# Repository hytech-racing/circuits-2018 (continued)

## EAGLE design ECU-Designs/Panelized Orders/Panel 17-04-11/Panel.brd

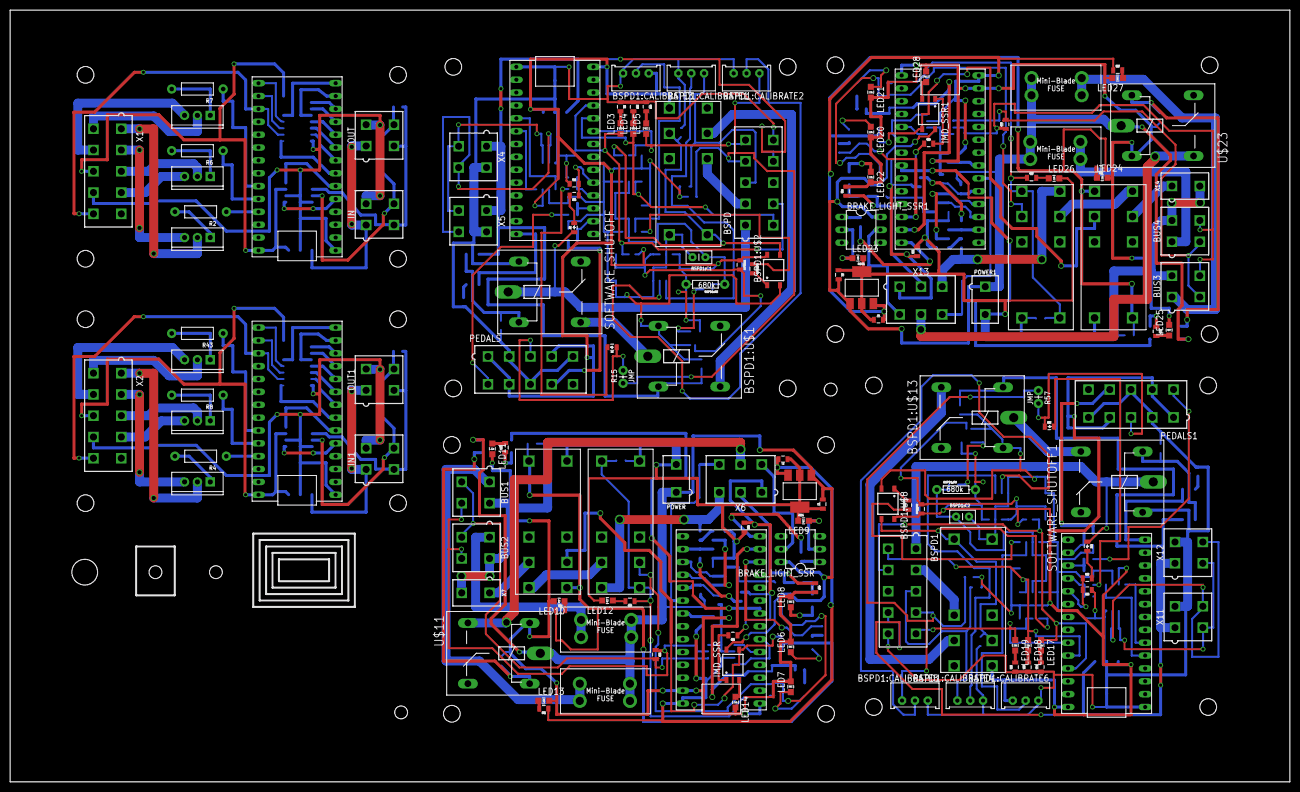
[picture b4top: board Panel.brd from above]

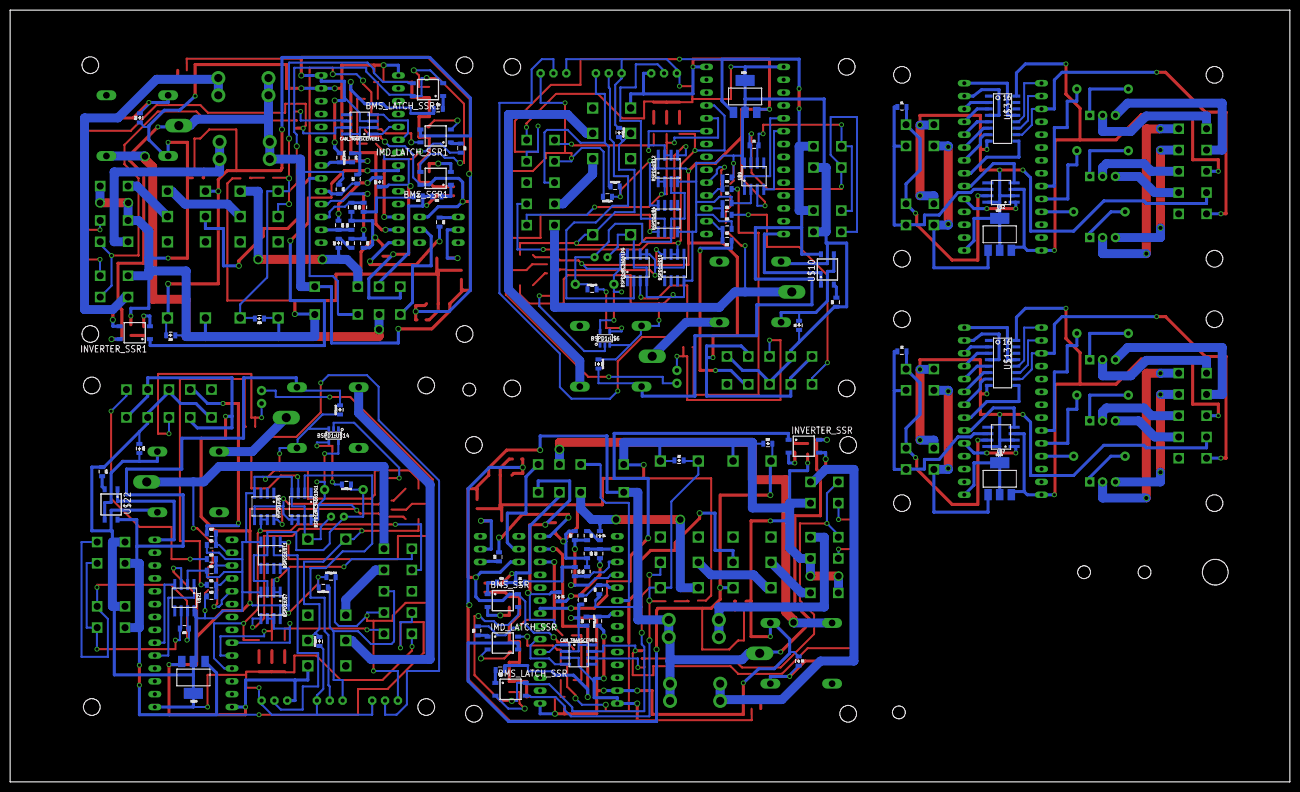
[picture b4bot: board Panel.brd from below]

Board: 2 copper layers, 252.7 x 152.4 mm, 242 parts (102 on the bottom side), 238 nets.

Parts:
BMS_LATCH_SSR, BMS_LATCH_SSR1: CPC1002N; SOP04
BMS_SSR, BMS_SSR1: CPC1002N; SOP04
BOARD_TEMP, BOARD_TEMP1: THERMISTOR_NCP21; 0805
BRAKE_LIGHT_SSR, BRAKE_LIGHT_SSR1: SOLID_STATE_RELAY_VO14642AT; DIL06
BSPD, BSPD1: MINIFIT_5566-10
BSPD1:C1, BSPD1:C2: .47u; CAP-PTH-SMALLEZ
BSPD1:CALIBRATE1, BSPD1:CALIBRATE2, BSPD1:CALIBRATE3, BSPD1:CALIBRATE4, BSPD1:CALIBRATE5, BSPD1:CALIBRATE6: TRIMPOT_3296
BSPD1:D1, BSPD1:D2, BSPD1:D3, BSPD1:D4: DIODE0805; 0805_D
BSPD1:MC34161DG, BSPD1:MC34161DG1: SOIC-08
BSPD1:R1, BSPD1:R2, BSPD1:R4, BSPD1:R7, BSPD1:R11, BSPD1:R12: 10k; 0805
BSPD1:R3, BSPD1:R8: 330; 0805
BSPD1:R5, BSPD1:R9: 680k; AXIAL-0.3EZ
BSPD1:R6, BSPD1:R10: 680; 0805
BSPD1:U$1, BSPD1:U$13: G5LE; ZF112
BSPD1:U$2, BSPD1:U$8: CPC1002N; SOP04
BSPD1:U$3, BSPD1:U$9: JW2SN-DC5V; JW2SN
BSPD1:U$4, BSPD1:U$5, BSPD1:U$7, BSPD1:U$10, BSPD1:U$11, BSPD1:U$12: MCP6002SOIC; SOIC-08
BSPD1:U$6, BSPD1:U$14: SN74LVC1G07; SOT-23-5
BUS1, BUS2, BUS3, BUS4: MINIFIT_5566-4
C1, C3: .22uF; 0805
C2, C4: .1uF; 0805
CAN_TRANSCEIVER, CAN_TRANSCEIVER1: MCP2551; SOIC-08
D2, D3, D4, D5, D6, D7, D8, D9, D10, D12, D13, D14, D15, D16, D17, D18, D19, D20: DIODE0805; 0805_D
FUSE_BUS_1, FUSE_BUS_2, FUSE_BUS_3, FUSE_BUS_4: 5A; MINI-BLADE_FUSE_HOLDER
IMD_LATCH_SSR, IMD_LATCH_SSR1: CPC1002N; SOP04
IMD_SHUTDOWN, IMD_SHUTDOWN1, IMD_SHUTDOWN2, IMD_SHUTDOWN3: G2RL-2-DC12; G2RL-2
IMD_SSR, IMD_SSR1: CPC1002N; SOP04
IN, IN1: MINIFIT_5566-4
INVERTER_SSR, INVERTER_SSR1: CPC1002N; SOP04
LED3, LED4, LED5, LED6, LED7, LED8, LED9, LED10, LED11, LED12, LED13, LED14, LED17, LED18, LED19, LED20, LED21, LED22, LED23, LED24, LED25, LED26, LED27, LED28: LED-805
OUT, OUT1: MINIFIT_5566-4
PEDALS, PEDALS1: MINIFIT_5566-10
POWER, POWER1: MINIFIT_5566-2
R1, R3, R5, R28, R50, R70: 120; 0805
R2, R4, R6, R7, R8, R43: AXIAL-0.4
R9, R13, R14, R54, R55, R56: 150; 0805
R10, R11, R12, R51, R52, R53: 15k; 0805
R15, R57: JMP; AXIAL-0.1
R16, R23, R24, R25, R26, R37, R58, R65, R66, R67, R68, R79: 100; 0805
R17, R18, R19, R36, R39, R59, R60, R61, R78, R81: 10k; 0805
R20, R22, R30, R32, R34, R62, R64, R72, R74, R76: 43k; 0805
R21, R29, R31, R33, R35, R63, R71, R73, R75, R77: 12k; 0805
R27, R38, R69, R80: 820; 0805
R40, R82: 2.2k; 0805
R41, R83: 270; 0805
R42, R84: 680; 0805
REG, REG1: 5V; SOT223
SOFTWARE_SHUTOFF, SOFTWARE_SHUTOFF1: G5LE; ZF112
T1, T2, T3, T4, T5, T6: N-CHANNEL_MOSFETGENERIC; TO-220-SINK
U$1, U$4, U$6, U$12, U$19, U$24: TEENSY_3.2_SIMPLE
U$2, U$7, U$9, U$21: MCP2551; SOIC-08
U$3, U$13: CD4040BSOIC; SOIC-16
U$5, U$8, U$14, U$20: SOT223
U$10, U$22: CPC1002N; SOP04
U$11, U$23: G5LE; ZF112
X1, X2: CONNECTOR-10; MINIFIT_5566-10
X4, X5, X11, X12: MINIFIT_5566-4
X6, X13: MINIFIT_5566-6
X7, X14: MINIFIT_5566-2

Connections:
12VSUPPLY_READ: R34.2, R35.1, U$12.A3
12VSUPPLY_READ1: R76.2, R77.1, U$24.A3
12V_F1: BUS1.1, FUSE_BUS_1.L1, FUSE_BUS_1.L2
12V_F2: BUS2.1, FUSE_BUS_2.R1, FUSE_BUS_2.R2
12V_F3: BUS3.1, FUSE_BUS_3.L1, FUSE_BUS_3.L2
12V_F4: BUS4.1, FUSE_BUS_4.R1, FUSE_BUS_4.R2
+5V: BSPD1:CALIBRATE3.1, BSPD1:MC34161DG.8, BSPD1:R1.1, BSPD1:R4.1, BSPD1:R5.P$2, BSPD1:R7.2, BSPD1:U$2.4, BSPD1:U$3.4, BSPD1:U$4.8, BSPD1:U$6.5, BSPD1:U$10.8, BSPD1:U$12.8, PEDALS.1, PEDALS.4, PEDALS.7, U$4.VIN, U$8.3, U$9.3
+5V1: BOARD_TEMP.1, C2.2, CAN_TRANSCEIVER.3, R41.1, REG.3, U$12.VIN
+5V2: BSPD1:CALIBRATE6.1, BSPD1:MC34161DG1.8, BSPD1:R2.1, BSPD1:R9.P$2, BSPD1:R11.1, BSPD1:R12.2, BSPD1:U$5.8, BSPD1:U$7.8, BSPD1:U$8.4, BSPD1:U$9.4, BSPD1:U$11.8, BSPD1:U$14.5, PEDALS1.1, PEDALS1.4, PEDALS1.7, U$19.VIN, U$20.3, U$21.3
+5V3: BOARD_TEMP1.1, C4.2, CAN_TRANSCEIVER1.3, R83.1, REG1.3, U$24.VIN
+5V4: U$1.VIN, U$2.3, U$3.16, U$5.3, X1.8
+5V5: U$6.VIN, U$7.3, U$13.16, U$14.3, X2.8
+12V: IN.1, OUT.1, U$5.1
+12V1: BSPD.9, BSPD1:D2.C, BSPD1:U$1.2, U$8.1, U$10.4, X4.1, X5.1
+12V2: BMS_SSR.4, BRAKE_LIGHT_SSR.6, C1.2, FUSE_BUS_1.R1, FUSE_BUS_1.R2, FUSE_BUS_2.L1, FUSE_BUS_2.L2, IMD_SSR.4, INVERTER_SSR.4, POWER.1, R34.1, REG.1, U$11.P
+12V3: IN1.1, OUT1.1, U$14.1
+12V4: BSPD1.9, BSPD1:D4.C, BSPD1:U$13.2, U$20.1, U$22.4, X11.1, X12.1
+12V5: BMS_SSR1.4, BRAKE_LIGHT_SSR1.6, C3.2, FUSE_BUS_3.R1, FUSE_BUS_3.R2, FUSE_BUS_4.L1, FUSE_BUS_4.L2, IMD_SSR1.4, INVERTER_SSR1.4, POWER1.1, R76.1, REG1.1, U$23.P
BMS_COIL_PWR: BMS_LATCH_SSR.3, D9.C, IMD_SHUTDOWN1.4, IMD_SHUTDOWN1.COIL-, R38.1
BMS_COIL_PWR1: BMS_LATCH_SSR1.3, D19.C, IMD_SHUTDOWN3.4, IMD_SHUTDOWN3.COIL-, R80.1
BMS_OK: D6.A, R24.2, R39.1, X6.2
BMS_OK1: D16.A, R66.2, R81.1, X13.2
BMS_OK_READ: R30.2, R31.1, U$12.A1
BMS_OK_READ1: R72.2, R73.1, U$24.A1
BMS_PWR_STEP: BMS_LATCH_SSR.4, BMS_SSR.3, IMD_SHUTDOWN1.3
BMS_PWR_STEP1: BMS_LATCH_SSR1.4, BMS_SSR1.3, IMD_SHUTDOWN3.3
BSPD1:N$1: BSPD1:D1.C, BSPD1:U$2.3, BSPD1:U$3.3, BSPD1:U$3.COIL-, BSPD1:U$12.5
BSPD1:N$2: BSPD1:R3.2, BSPD1:U$6.4
BSPD1:N$3: BSPD1:R6.2, BSPD1:U$2.1
BSPD1:N$4: BSPD1:CALIBRATE5.2, BSPD1:MC34161DG1.3
BSPD1:N$5: BSPD1:CALIBRATE2.2, BSPD1:MC34161DG.3
BSPD1:N$6: BSPD1:CALIBRATE1.2, BSPD1:MC34161DG.2
BSPD1:N$7: BSPD1:CALIBRATE3.2, BSPD1:U$4.2
BSPD1:N$8: BSPD1:CALIBRATE4.2, BSPD1:MC34161DG1.2
BSPD1:N$9: BSPD1:R6.1, BSPD1:U$4.1
BSPD1:N$10: BSPD1:MC34161DG.5, BSPD1:MC34161DG.6, BSPD1:R1.2, BSPD1:U$6.2, BSPD1:U$10.5
BSPD1:N$11: BSPD1:R10.1, BSPD1:U$11.1
BSPD1:N$12: BSPD1:C2.1, BSPD1:R8.1, BSPD1:R9.P$1, BSPD1:U$7.3, BSPD1:U$11.3
BSPD1:N$13: BSPD1:C1.1, BSPD1:R3.1, BSPD1:R5.P$1, BSPD1:U$4.3, BSPD1:U$12.3
BSPD1:N$14: BSPD1:CALIBRATE6.2, BSPD1:U$11.2
BSPD1:N$15: BSPD1:D3.C, BSPD1:U$7.5, BSPD1:U$8.3, BSPD1:U$9.3, BSPD1:U$9.COIL-
BSPD1:N$16: BSPD1:MC34161DG1.5, BSPD1:MC34161DG1.6, BSPD1:R2.2, BSPD1:U$5.5, BSPD1:U$14.2
BSPD1:N$17: BSPD1:R8.2, BSPD1:U$14.4
BSPD1:N$18: BSPD1:R10.2, BSPD1:U$8.1
BSPD1:SHUTDOWN_C: BSPD1:U$1.S, BSPD1:U$3.6
BSPD1:SHUTDOWN_C1: BSPD1:U$9.6, BSPD1:U$13.S
CANH: BUS1.4, BUS2.4, CAN_TRANSCEIVER.7, R28.1
CANH1: BUS3.4, BUS4.4, CAN_TRANSCEIVER1.7, R70.1
CANH2: IN.4, OUT.4, R1.2, U$2.7
CANH3: IN1.4, OUT1.4, R3.2, U$7.7
CANL: BUS1.3, BUS2.3, CAN_TRANSCEIVER.6, R28.2
CANL1: BUS3.3, BUS4.3, CAN_TRANSCEIVER1.6, R70.2
CANL2: IN.3, OUT.3, R1.1, U$2.6
CANL3: IN1.3, OUT1.3, R3.1, U$7.6
FAN1-: T1.2, X1.1
FAN1-1: T4.2, X2.1
FAN2-: T2.2, X1.3
FAN2-1: T5.2, X2.3
FAN3-: T3.2, X1.6
FAN3-1: T6.2, X2.6
GND: IN.2, OUT.2, U$1.GND, U$2.2, U$2.8, U$3.8, U$5.2, U$5.4, X1.9
GND1: BSPD.10, BSPD1:C1.2, BSPD1:CALIBRATE1.3, BSPD1:CALIBRATE2.3, BSPD1:CALIBRATE3.3, BSPD1:D1.A, BSPD1:D2.A, BSPD1:MC34161DG.4, BSPD1:MC34161DG.7, BSPD1:U$1.1, BSPD1:U$2.2, BSPD1:U$3.COIL+, BSPD1:U$4.4, BSPD1:U$6.3, BSPD1:U$10.4, BSPD1:U$12.4, D4.A, PEDALS.2, PEDALS.5, PEDALS.8, R9.1, R10.1, R11.1, R12.1, R13.1, R14.1, R16.1, R21.1, SOFTWARE_SHUTOFF.1, U$4.GND, U$8.2, U$8.4, U$9.2, U$9.8, X4.2, X5.2
GND2: BUS1.2, BUS2.2, C1.1, C2.1, CAN_TRANSCEIVER.2, CAN_TRANSCEIVER.8, D8.A, D9.A, D10.A, IMD_SHUTDOWN.COIL+, IMD_SHUTDOWN1.COIL+, LED6.C, LED7.C, LED8.C, LED9.C, LED10.C, LED11.C, LED12.C, LED13.C, LED14.C, POWER.2, R29.2, R31.2, R33.2, R35.2, R36.1, R39.2, R40.2, REG.2, REG.4, U$11.2, U$12.AGND, U$12.GND, X7.2
GND3: T1.3, X1.2
GND4: BSPD1.10, BSPD1:C2.2, BSPD1:CALIBRATE4.3, BSPD1:CALIBRATE5.3, BSPD1:CALIBRATE6.3, BSPD1:D3.A, BSPD1:D4.A, BSPD1:MC34161DG1.4, BSPD1:MC34161DG1.7, BSPD1:U$5.4, BSPD1:U$7.4, BSPD1:U$8.2, BSPD1:U$9.COIL+, BSPD1:U$11.4, BSPD1:U$13.1, BSPD1:U$14.3, D14.A, PEDALS1.2, PEDALS1.5, PEDALS1.8, R51.1, R52.1, R53.1, R54.1, R55.1, R56.1, R58.1, R63.1, SOFTWARE_SHUTOFF1.1, U$19.GND, U$20.2, U$20.4, U$21.2, U$21.8, X11.2, X12.2
GND5: BUS3.2, BUS4.2, C3.1, C4.1, CAN_TRANSCEIVER1.2, CAN_TRANSCEIVER1.8, D18.A, D19.A, D20.A, IMD_SHUTDOWN2.COIL+, IMD_SHUTDOWN3.COIL+, LED20.C, LED21.C, LED22.C, LED23.C, LED24.C, LED25.C, LED26.C, LED27.C, LED28.C, POWER1.2, R71.2, R73.2, R75.2, R77.2, R78.1, R81.2, R82.2, REG1.2, REG1.4, U$23.2, U$24.AGND, U$24.GND, X14.2
GND6: T2.3, X1.4
GND7: T3.3, X1.7
GND8: IN1.2, OUT1.2, U$6.GND, U$7.2, U$7.8, U$13.8, U$14.2, U$14.4, X2.9
GND9: T4.3, X2.2
GND10: T5.3, X2.4
GND11: T6.3, X2.7
INVERTER_SUPPLY: U$11.S, X6.5
INVERTER_SUPPLY1: U$23.S, X13.5
unnamed: R2.P$2, T1.1
unnamed: U$1.D3(CANTX), U$2.1
unnamed: U$1.D4(CANRX), U$2.4
unnamed: R6.P$2, T2.1
unnamed: R7.P$1, U$1.A7
unnamed: R7.P$2, T3.1
unnamed: U$1.D7(RX3), U$3.6
unnamed: U$6.D3(CANTX), U$7.1
unnamed: U$6.D4(CANRX), U$7.4
unnamed: R4.P$2, T4.1
unnamed: R8.P$2, T5.1
unnamed: U$1.D5, U$3.9
unnamed: U$1.D6, U$3.7
unnamed: R5.2, U$9.6, X4.3, X5.3
unnamed: U$1.D8(TX3), U$3.5
unnamed: U$1.D9(RX2), U$3.3
unnamed: U$1.D10(TX2), U$3.2
unnamed: R2.P$1, U$1.A9
unnamed: R6.P$1, U$1.A8
unnamed: R5.1, U$9.7, X4.4, X5.4
unnamed: U$1.D11, U$3.4
unnamed: U$1.D12, U$3.13
unnamed: U$1.A0, U$3.11
unnamed: U$1.D13, U$3.12
unnamed: R43.P$2, T6.1
unnamed: U$4.D4(CANRX), U$9.4
unnamed: U$4.D3(CANTX), U$9.1
unnamed: PEDALS.6, R18.1
unnamed: R10.2, R17.2, U$4.A0
unnamed: LED3.C, R9.2
unnamed: LED4.C, R13.2
unnamed: LED5.C, R14.2
unnamed: R16.2, U$10.2
unnamed: R11.2, R18.2, U$4.A1
unnamed: PEDALS.9, R17.1
unnamed: R12.2, R19.2, U$4.A2
unnamed: D2.A, PEDALS.3, R15.P$2
unnamed: D2.C, R19.1
unnamed: D4.C, SOFTWARE_SHUTOFF.2, U$10.3
unnamed: D3.C, R20.2
unnamed: CAN_TRANSCEIVER.4, U$12.D4(CANRX)
unnamed: CAN_TRANSCEIVER.1, U$12.D3(CANTX)
unnamed: D10.C, IMD_LATCH_SSR.3, IMD_SHUTDOWN.4, IMD_SHUTDOWN.COIL-, R27.1
unnamed: R23.2, U$12.D12
unnamed: BRAKE_LIGHT_SSR.5, X6.4
unnamed: BOARD_TEMP.2, R36.2, U$12.A5
unnamed: R26.1, U$12.D11
unnamed: IMD_LATCH_SSR.2, LED6.A
unnamed: BMS_SSR.2, LED8.A
unnamed: BMS_SSR.1, R24.1
unnamed: BRAKE_LIGHT_SSR.2, LED9.A
unnamed: BRAKE_LIGHT_SSR.1, R23.1
unnamed: LED10.A, R27.2
unnamed: INVERTER_SSR.1, U$12.D6
unnamed: U$12.A4, X6.6
unnamed: D5.C, R22.1
unnamed: D6.C, R30.1
unnamed: D7.C, R32.1
unnamed: D8.C, INVERTER_SSR.3, U$11.1
unnamed: INVERTER_SSR.2, R37.1
unnamed: LED11.A, R37.2
unnamed: IMD_LATCH_SSR.1, R25.1
unnamed: R25.2, U$12.D10(TX2)
unnamed: BMS_LATCH_SSR.2, LED7.A
unnamed: BMS_LATCH_SSR.1, R26.2
unnamed: LED12.A, R38.2
unnamed: LED13.A, R41.2
unnamed: IMD_LATCH_SSR.4, IMD_SHUTDOWN.3, IMD_SSR.3
unnamed: IMD_SSR.2, LED14.A
unnamed: IMD_SSR.1, R42.2
unnamed: R4.P$1, U$6.A9
unnamed: R8.P$1, U$6.A8
unnamed: R43.P$1, U$6.A7
unnamed: U$6.D5, U$13.9
unnamed: U$6.D6, U$13.7
unnamed: U$6.D7(RX3), U$13.6
unnamed: U$6.D8(TX3), U$13.5
unnamed: U$6.D9(RX2), U$13.3
unnamed: U$6.D10(TX2), U$13.2
unnamed: U$6.D11, U$13.4
unnamed: U$6.D12, U$13.13
unnamed: U$6.A0, U$13.11
unnamed: U$6.D13, U$13.12
unnamed: R50.2, U$21.6, X11.3, X12.3
unnamed: R50.1, U$21.7, X11.4, X12.4
unnamed: U$19.D4(CANRX), U$21.4
unnamed: U$19.D3(CANTX), U$21.1
unnamed: PEDALS1.6, R60.1
unnamed: R51.2, R59.2, U$19.A0
unnamed: LED17.C, R54.2
unnamed: LED18.C, R55.2
unnamed: LED19.C, R56.2
unnamed: R58.2, U$22.2
unnamed: R52.2, R60.2, U$19.A1
unnamed: PEDALS1.9, R59.1
unnamed: R53.2, R61.2, U$19.A2
unnamed: D12.A, PEDALS1.3, R57.P$2
unnamed: D12.C, R61.1
unnamed: D14.C, SOFTWARE_SHUTOFF1.2, U$22.3
unnamed: D13.C, R62.2
unnamed: CAN_TRANSCEIVER1.4, U$24.D4(CANRX)
unnamed: CAN_TRANSCEIVER1.1, U$24.D3(CANTX)
unnamed: D20.C, IMD_LATCH_SSR1.3, IMD_SHUTDOWN2.4, IMD_SHUTDOWN2.COIL-, R69.1
unnamed: R65.2, U$24.D12
unnamed: BRAKE_LIGHT_SSR1.5, X13.4
unnamed: BOARD_TEMP1.2, R78.2, U$24.A5
unnamed: R68.1, U$24.D11
unnamed: IMD_LATCH_SSR1.2, LED20.A
unnamed: BMS_SSR1.2, LED22.A
unnamed: BMS_SSR1.1, R66.1
unnamed: BRAKE_LIGHT_SSR1.2, LED23.A
unnamed: BRAKE_LIGHT_SSR1.1, R65.1
unnamed: LED24.A, R69.2
unnamed: INVERTER_SSR1.1, U$24.D6
unnamed: U$24.A4, X13.6
unnamed: D15.C, R64.1
unnamed: D16.C, R72.1
unnamed: D17.C, R74.1
unnamed: D18.C, INVERTER_SSR1.3, U$23.1
unnamed: INVERTER_SSR1.2, R79.1
unnamed: LED25.A, R79.2
unnamed: IMD_LATCH_SSR1.1, R67.1
unnamed: R67.2, U$24.D10(TX2)
unnamed: BMS_LATCH_SSR1.2, LED21.A
unnamed: BMS_LATCH_SSR1.1, R68.2
unnamed: LED26.A, R80.2
unnamed: LED27.A, R83.2
unnamed: IMD_LATCH_SSR1.4, IMD_SHUTDOWN2.3, IMD_SSR1.3
unnamed: IMD_SSR1.2, LED28.A
unnamed: IMD_SSR1.1, R84.2
OKHS: D5.A, R40.1, R42.1, X6.1
OKHS1: D15.A, R82.1, R84.1, X13.1
OKHS_READ: R22.2, R29.1, U$12.A0
OKHS_READ1: R64.2, R71.1, U$24.A0
PULSE: U$1.A1, U$3.10, X1.10
PULSE1: U$6.A1, U$13.10, X2.10
READ_CHARGE: BSPD.6, BSPD1:U$12.1, BSPD1:U$12.2, LED4.A, U$4.A8
READ_CHARGE1: BSPD1.6, BSPD1:U$7.1, BSPD1:U$7.2, LED18.A, U$19.A8
READ_FAULT: BSPD.5, BSPD1:U$12.6, BSPD1:U$12.7, LED5.A, U$4.A7
READ_FAULT1: BSPD1.5, BSPD1:U$7.6, BSPD1:U$7.7, LED19.A, U$19.A7
READ_SWITCH: BSPD.7, BSPD1:U$10.6, BSPD1:U$10.7, LED3.A, U$4.A9
READ_SWITCH1: BSPD1.7, BSPD1:U$5.6, BSPD1:U$5.7, LED17.A, U$19.A9
READ_UPSTREAM_SHUTDOWN: R20.1, R21.2, U$4.A3
READ_UPSTREAM_SHUTDOWN1: R62.1, R63.2, U$19.A3
SHUTDOWN_A: BSPD.1, D3.A, SOFTWARE_SHUTOFF.P
SHUTDOWN_A1: IMD_SHUTDOWN.5, IMD_SHUTDOWN1.6
SHUTDOWN_A2: BSPD1.1, D13.A, SOFTWARE_SHUTOFF1.P
SHUTDOWN_A3: IMD_SHUTDOWN2.5, IMD_SHUTDOWN3.6
SHUTDOWN_B: BSPD1:U$1.P, SOFTWARE_SHUTOFF.S
SHUTDOWN_B1: D7.A, IMD_SHUTDOWN1.5, X6.3
SHUTDOWN_B2: BSPD1:U$13.P, SOFTWARE_SHUTOFF1.S
SHUTDOWN_B3: D17.A, IMD_SHUTDOWN3.5, X13.3
SHUTDOWN_D: BSPD.2, BSPD1:U$3.7
SHUTDOWN_D1: BSPD1.2, BSPD1:U$9.7
SHUTDOWN_OUT_READ: R32.2, R33.1, U$12.A2
SHUTDOWN_OUT_READ1: R74.2, R75.1, U$24.A2
SHUTDOWN_POWER: IMD_SHUTDOWN.6, X7.1
SHUTDOWN_POWER1: IMD_SHUTDOWN2.6, X14.1
SHUTDOWN_RELAY_CTRL: U$4.D12, U$10.1
SHUTDOWN_RELAY_CTRL1: U$19.D12, U$22.1
SIGNAL_BRAKE: BSPD.4, BSPD1:CALIBRATE2.1, BSPD1:R4.2, R15.P$1
SIGNAL_BRAKE1: BSPD1.4, BSPD1:CALIBRATE5.1, BSPD1:R11.2, R57.P$1
SIGNAL_CURRENT: BSPD.3, BSPD1:CALIBRATE1.1, BSPD1:R7.1
SIGNAL_CURRENT1: BSPD1.3, BSPD1:CALIBRATE4.1, BSPD1:R12.1

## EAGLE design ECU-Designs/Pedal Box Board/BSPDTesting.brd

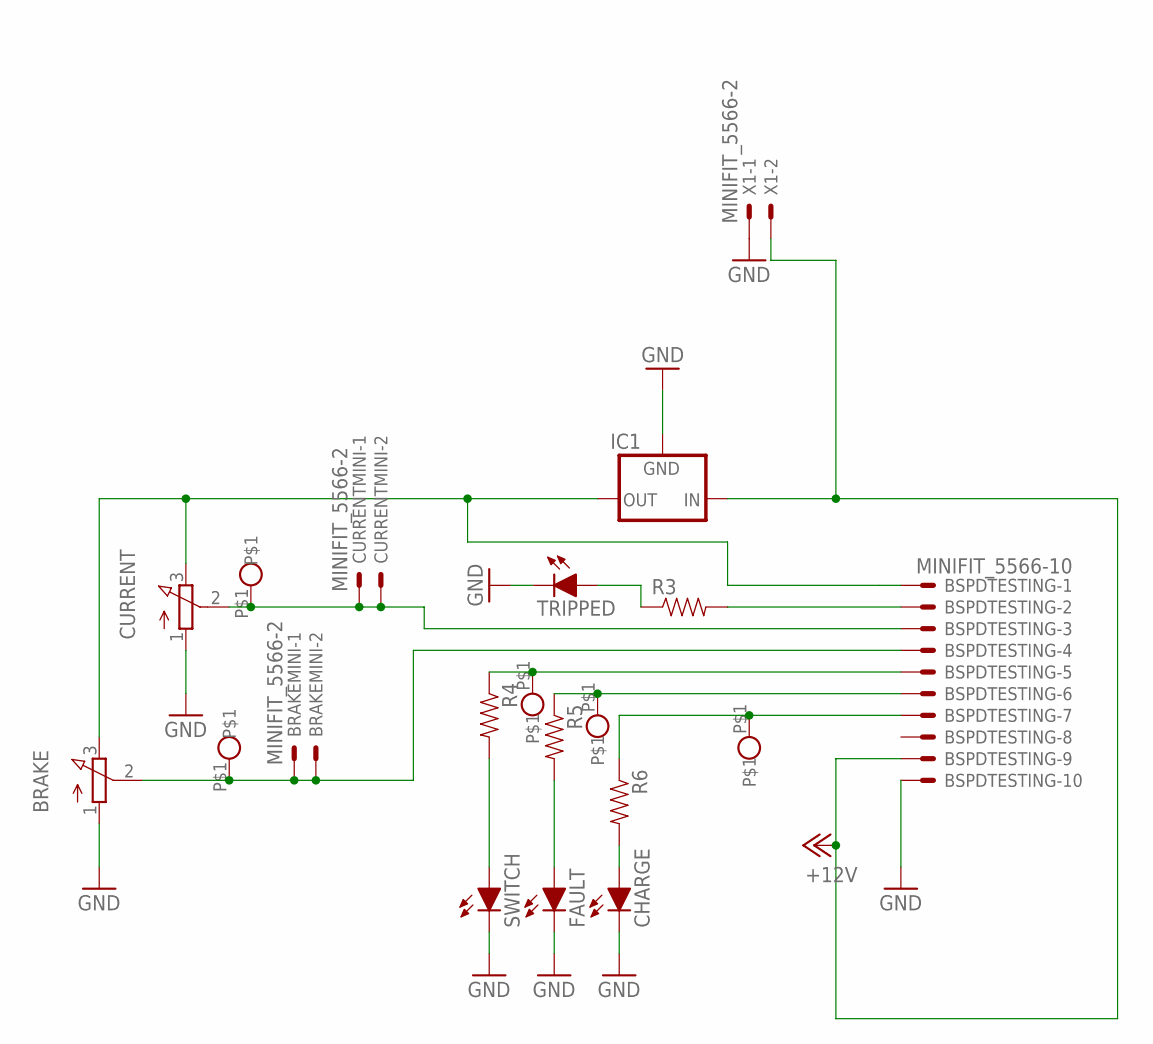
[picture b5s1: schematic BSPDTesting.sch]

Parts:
BRAKE: 3RP/1610N
BRAKEMINI: MINIFIT_5566-2
BSPDTESTING: MINIFIT_5566-10
CHARGE: LED-3MM
CURRENT: 3RP/1610N
CURRENTMINI: MINIFIT_5566-2
FAULT: LED-3MM
IC1: 5VREG_L7805_HOR; TO-220-H
R3, R4, R5, R6: RESISTORAXIAL-0.3; AXIAL-0.3
SWITCH: LED-3MM
TRIPPED: LED-3MM
U$1, U$2, U$3, U$4, U$5: TEST_POINT_COMPACT_THM
X1: MINIFIT_5566-2

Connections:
+12V: BSPDTESTING.9, IC1.1 (IN), X1.2
GND: BRAKE.1 (A), BSPDTESTING.10, CHARGE.K (C), CURRENT.1 (A), FAULT.K (C), IC1.2 (GND), SWITCH.K (C), TRIPPED.K (C), X1.1
unnamed: BSPDTESTING.5, R4.P$1 (1), U$3.P$1
unnamed: R4.P$2 (2), SWITCH.A
unnamed: BSPDTESTING.6, R5.P$1 (1), U$4.P$1
unnamed: FAULT.A, R5.P$2 (2)
unnamed: BSPDTESTING.7, R6.P$1 (1), U$5.P$1
unnamed: CHARGE.A, R6.P$2 (2)
unnamed: BSPDTESTING.2, R3.P$2 (2)
unnamed: R3.P$1 (1), TRIPPED.A
unnamed: BRAKE.2 (S), BRAKEMINI.1, BRAKEMINI.2, BSPDTESTING.4, U$1.P$1
unnamed: BSPDTESTING.3, CURRENT.2 (S), CURRENTMINI.1, CURRENTMINI.2, U$2.P$1
unnamed: BRAKE.3 (E), CURRENT.3 (E), IC1.3 (OUT)

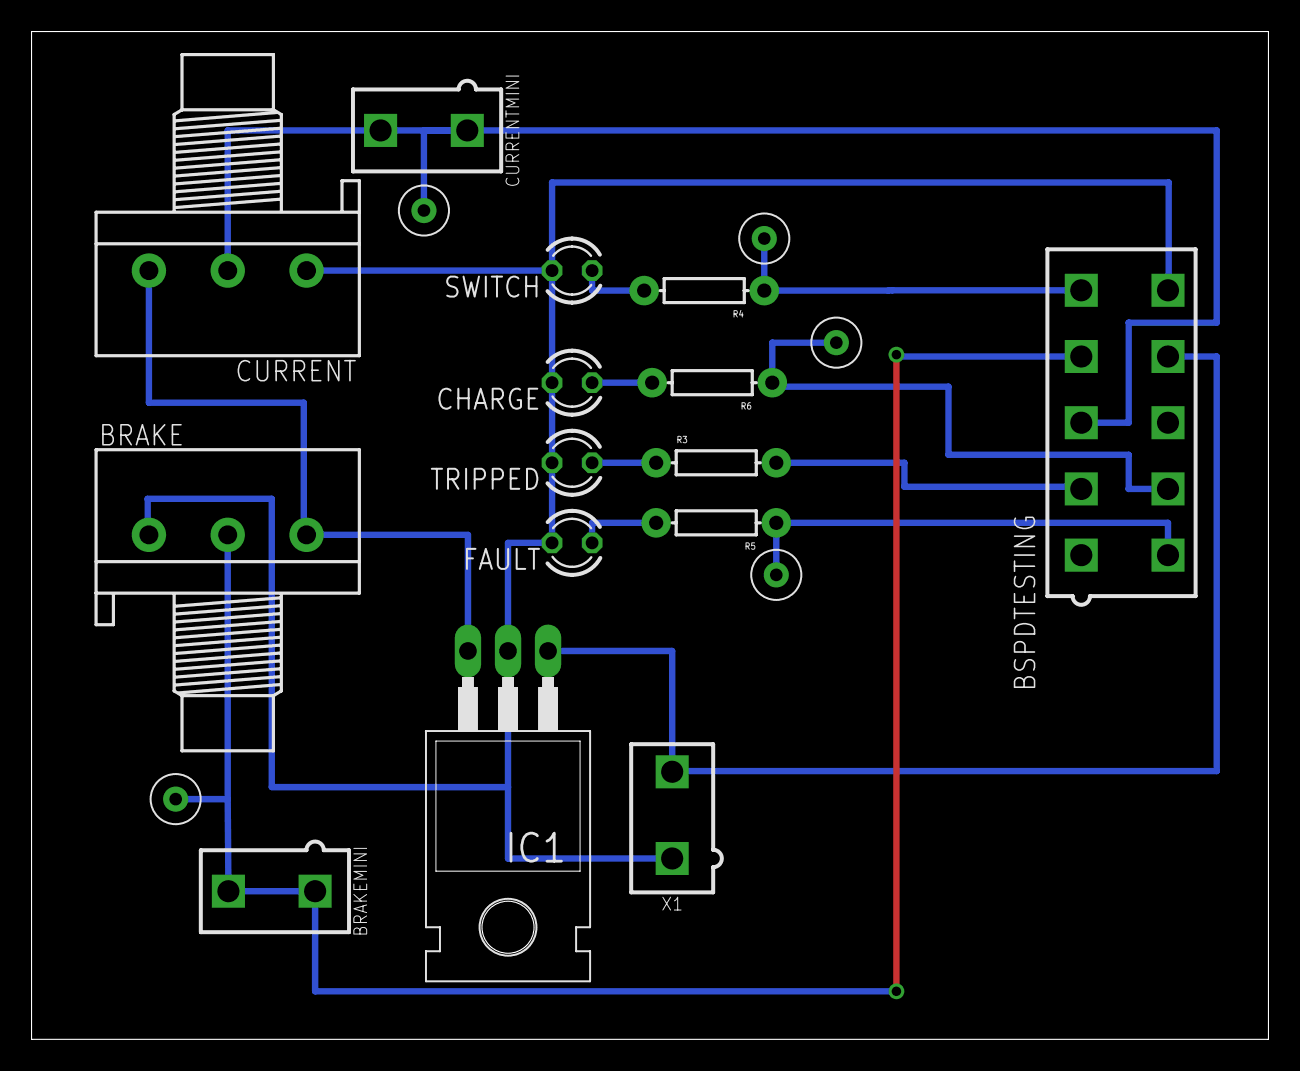
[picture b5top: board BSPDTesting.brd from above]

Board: 2 copper layers, 78.5 x 63.9 mm, 20 parts (0 on the bottom side), 13 nets.

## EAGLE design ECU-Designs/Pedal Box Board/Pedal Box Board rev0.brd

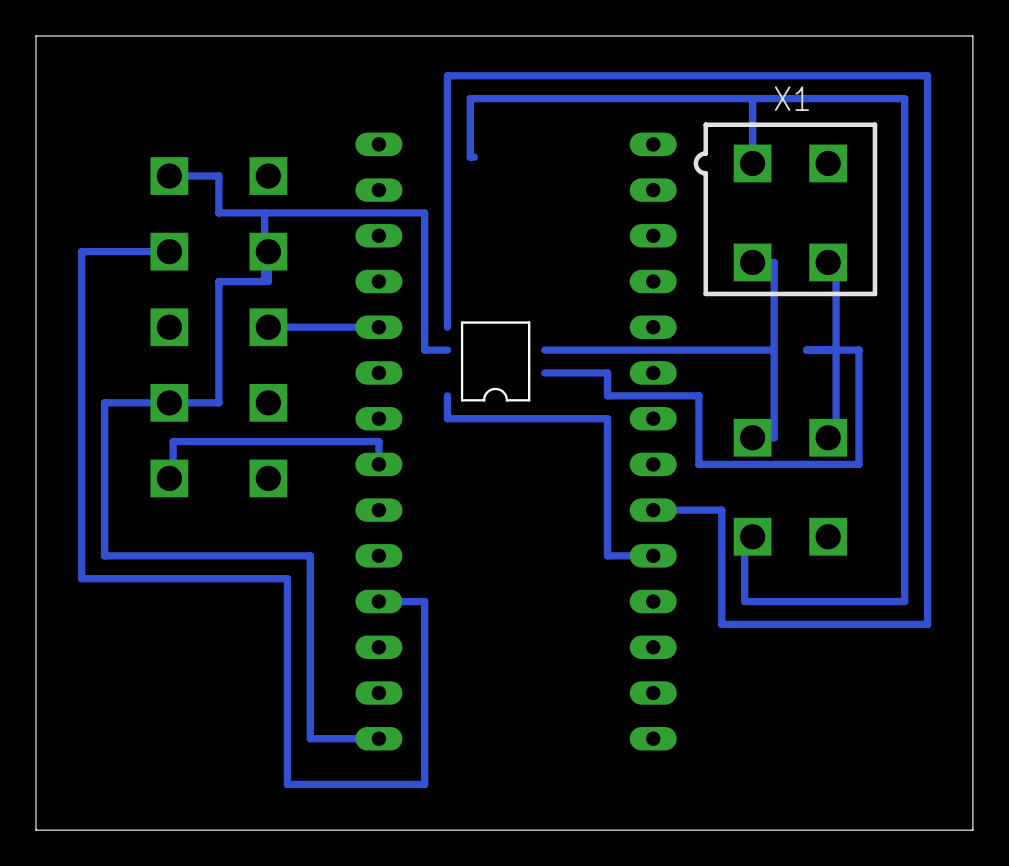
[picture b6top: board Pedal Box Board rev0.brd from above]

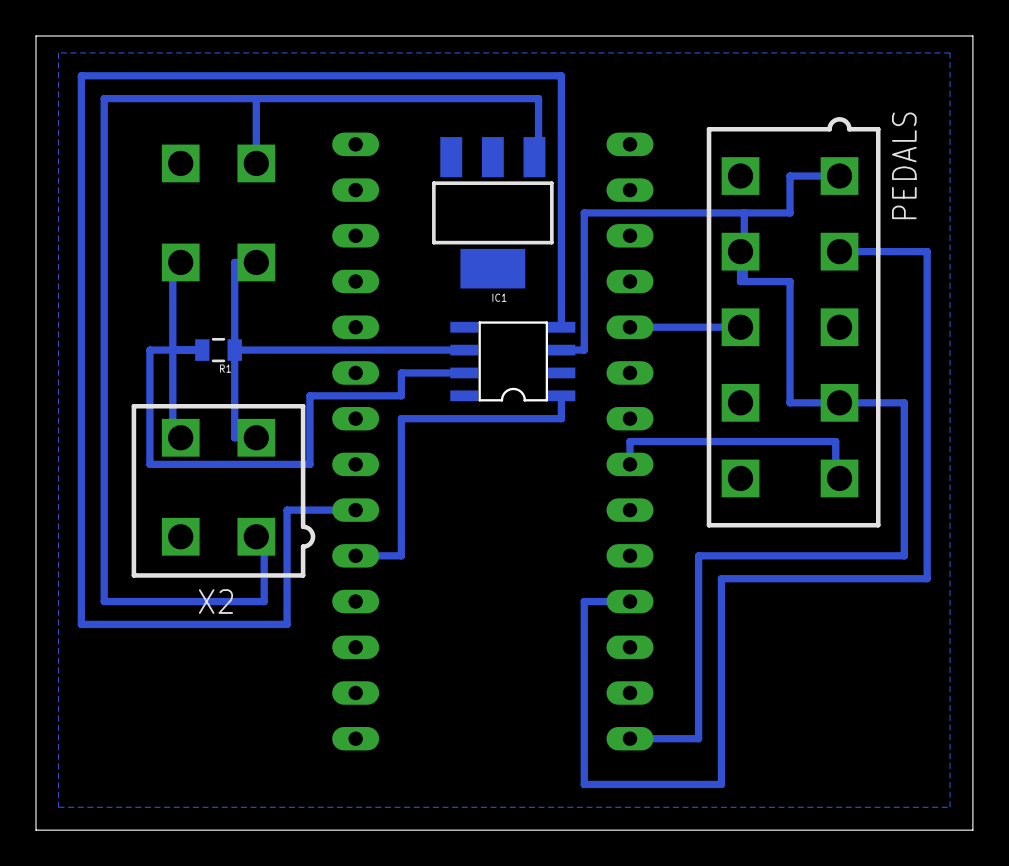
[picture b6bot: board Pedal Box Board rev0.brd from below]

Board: 2 copper layers, 52.0 x 44.1 mm, 7 parts (5 on the bottom side), 10 nets.

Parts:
IC1: SOT223
PEDALS: MINIFIT_5566-10
R1: 120; 0805
U$1: TEENSY_3.2_SIMPLE
U$2: MCP2551SOIC; SOIC08
X1, X2: MINIFIT_5566-4

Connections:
GND: IC1.2, IC1.4, PEDALS.3, PEDALS.6, PEDALS.9, U$1.GND, U$2.2, X2.2
unnamed: R1.2, U$2.7, X1.4, X2.4
unnamed: R1.1, U$2.6, X1.3, X2.3
unnamed: PEDALS.2, U$1.A9
unnamed: IC1.1, X1.1, X2.1
unnamed: PEDALS.5, U$1.A6
unnamed: PEDALS.8, U$1.A3
unnamed: PEDALS.1, PEDALS.4, PEDALS.7, U$1.VIN, U$2.3
unnamed: U$1.D4(CANRX), U$2.4
unnamed: U$1.D3(CANTX), U$2.1

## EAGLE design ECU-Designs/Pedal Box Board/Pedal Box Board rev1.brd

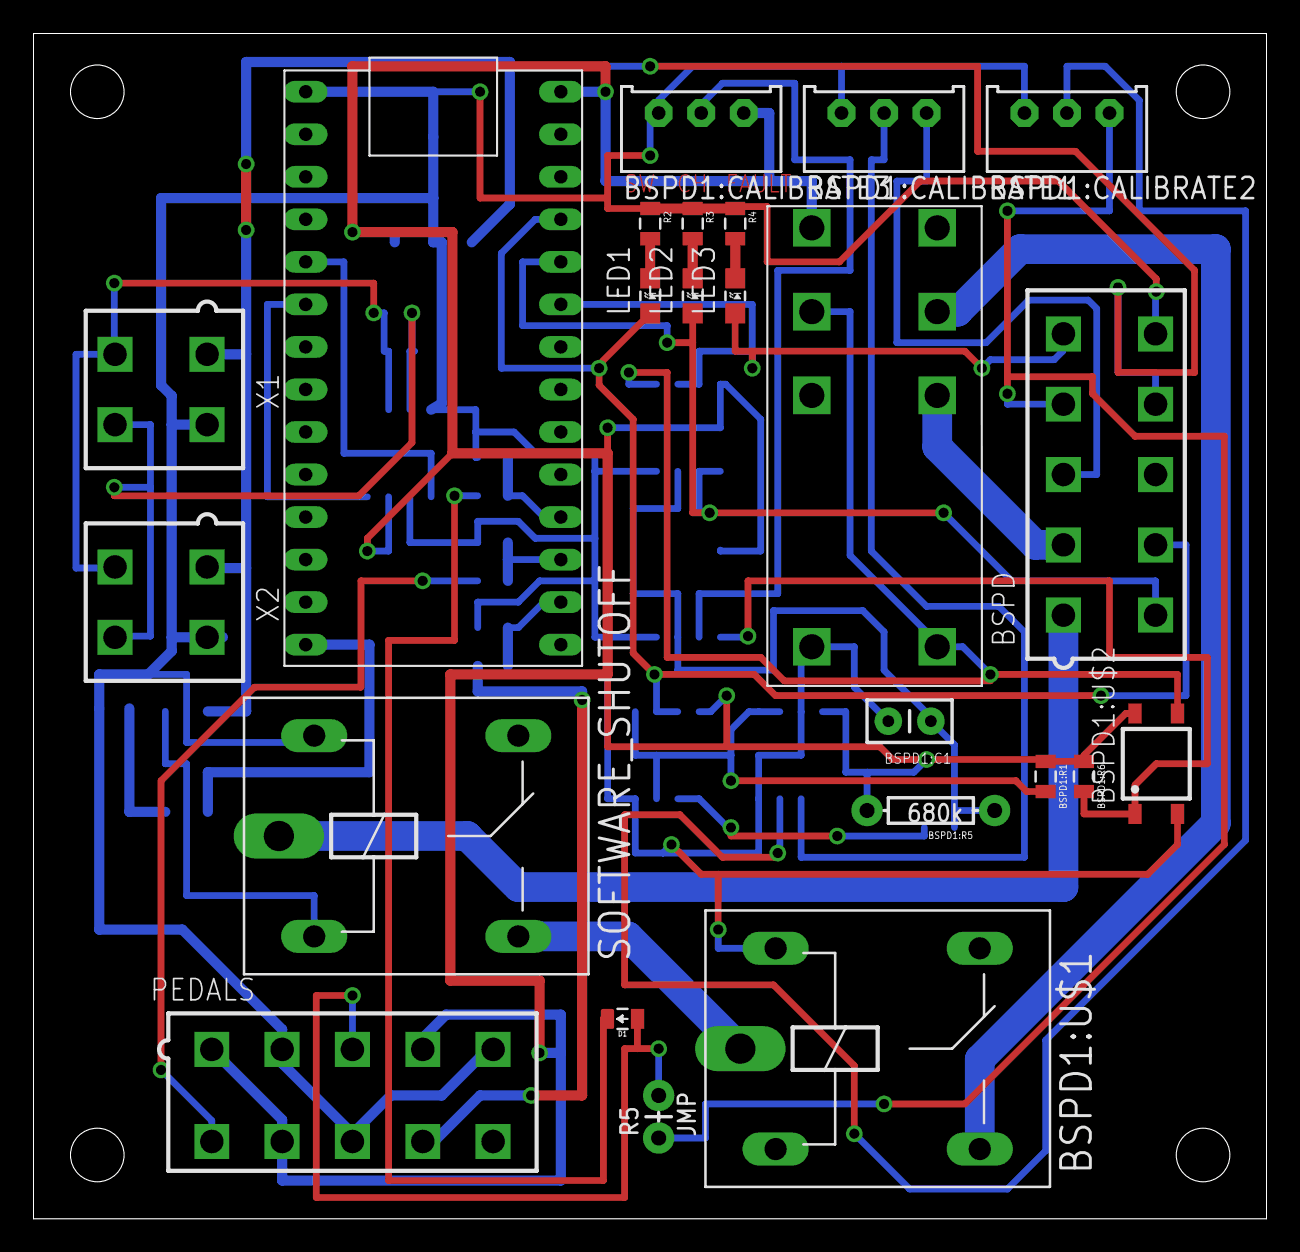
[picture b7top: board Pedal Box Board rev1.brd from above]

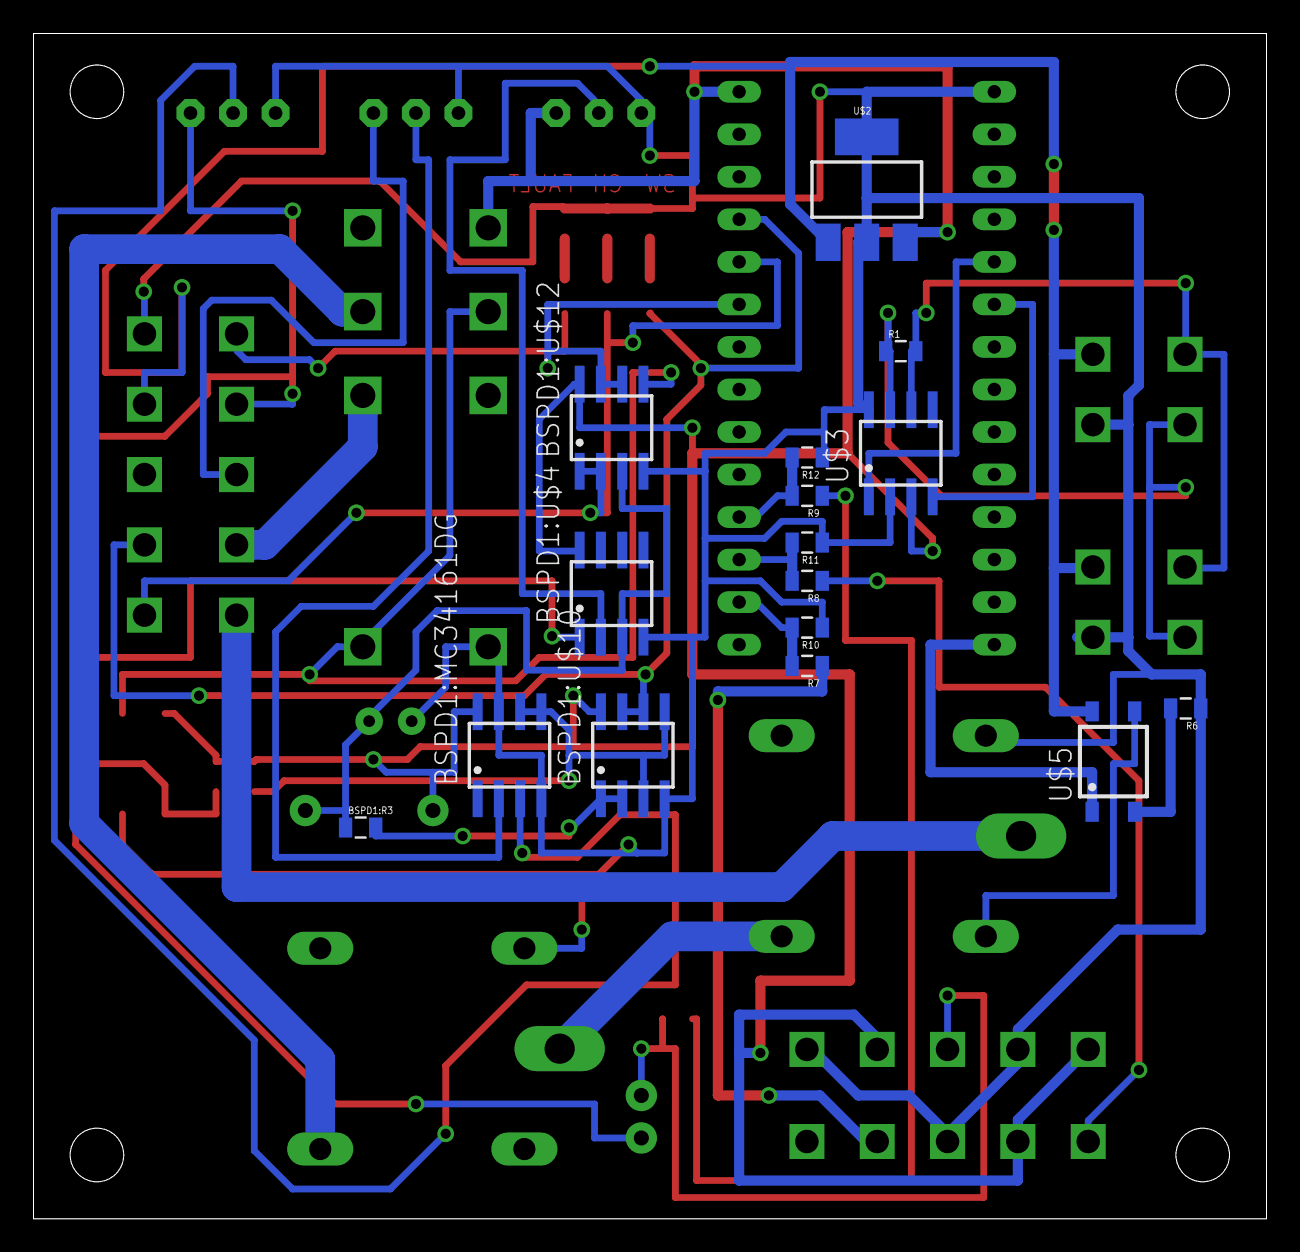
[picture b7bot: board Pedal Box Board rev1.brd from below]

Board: 2 copper layers, 73.6 x 70.8 mm, 40 parts (16 on the bottom side), 37 nets.

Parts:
BSPD: MINIFIT_5566-10
BSPD1:C1: .47u; CAP-PTH-SMALLEZ
BSPD1:CALIBRATE1, BSPD1:CALIBRATE2, BSPD1:CALIBRATE3: TRIMPOT_3296
BSPD1:MC34161DG: SOIC-08
BSPD1:R1: 10k; 0805
BSPD1:R3: 330; 0805
BSPD1:R5: 680k; AXIAL-0.3EZ
BSPD1:R6: 680; 0805
BSPD1:U$1: G5LE; ZF112
BSPD1:U$2: CPC1002N; SOP04
BSPD1:U$3: DPDT_RELAY_PANASONIC_JW2SN-DC5V; DPDT_RELAY_PANASONIC_JW2SN
BSPD1:U$4: LM293DG4; SOIC-08
BSPD1:U$10, BSPD1:U$12: MCP6002; SOIC-08
D1: DIODE0805; 0805_D
LED1, LED2, LED3: LED-805
PEDALS: MINIFIT_5566-10
R1: 120; 0805
R2, R3, R4: 150; 0805
R5: JMP; AXIAL-0.1
R6: 100; 0805
R7, R8, R9: 10k; 0805
R10, R11, R12: 15k; 0805
SOFTWARE_SHUTOFF: G5LE; ZF112
U$1: TEENSY_3.2_SIMPLE
U$2: SOT223
U$3: MCP2551; SOIC-08
U$5: CPC1002N; SOP04
X1, X2: MINIFIT_5566-4

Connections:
+5V: BSPD1:CALIBRATE3.1, BSPD1:MC34161DG.8, BSPD1:R1.1, BSPD1:R5.P$2, BSPD1:R6.1, BSPD1:U$2.4, BSPD1:U$3.4, BSPD1:U$4.8, BSPD1:U$10.8, BSPD1:U$12.8, PEDALS.1, PEDALS.4, PEDALS.7, U$1.VIN, U$2.3, U$3.3
+12V: BSPD.9, U$2.1, U$5.4, X1.1, X2.1
BSPD1:N$1: BSPD1:U$2.3, BSPD1:U$3.3, BSPD1:U$3.COIL-, BSPD1:U$12.5
BSPD1:N$4: BSPD1:R3.2, BSPD1:U$10.1, BSPD1:U$10.2
BSPD1:N$5: BSPD1:CALIBRATE2.2, BSPD1:MC34161DG.3
BSPD1:N$6: BSPD1:CALIBRATE1.2, BSPD1:MC34161DG.2
BSPD1:N$7: BSPD1:CALIBRATE3.2, BSPD1:U$4.2
BSPD1:N$9: BSPD1:R6.2, BSPD1:U$2.1, BSPD1:U$4.1
BSPD1:N$10: BSPD1:MC34161DG.5, BSPD1:MC34161DG.6, BSPD1:R1.2, BSPD1:U$10.3, BSPD1:U$10.5
BSPD1:N$13: BSPD1:C1.1, BSPD1:R3.1, BSPD1:R5.P$1, BSPD1:U$4.3, BSPD1:U$12.3
BSPD1:SHUTDOWN_C: BSPD1:U$1.S, BSPD1:U$3.6
GND: BSPD.10, BSPD1:C1.2, BSPD1:CALIBRATE1.3, BSPD1:CALIBRATE2.3, BSPD1:CALIBRATE3.3, BSPD1:MC34161DG.4, BSPD1:MC34161DG.7, BSPD1:U$1.1, BSPD1:U$2.2, BSPD1:U$3.COIL+, BSPD1:U$4.4, BSPD1:U$10.4, BSPD1:U$12.4, PEDALS.2, PEDALS.5, PEDALS.8, R2.1, R3.1, R4.1, R6.1, R10.1, R11.1, R12.1, SOFTWARE_SHUTOFF.1, U$1.GND, U$2.2, U$2.4, U$3.2, U$3.8, X1.2, X2.2
unnamed: PEDALS.9, R7.1
unnamed: U$1.D4(CANRX), U$3.4
unnamed: R1.2, U$3.6, X1.3, X2.3
unnamed: R1.1, U$3.7, X1.4, X2.4
unnamed: U$1.D3(CANTX), U$3.1
unnamed: R8.2, R11.2, U$1.A1
unnamed: D1.C, R9.1
unnamed: PEDALS.6, R8.1
unnamed: R7.2, R10.2, U$1.A0
unnamed: R9.2, R12.2, U$1.A2
unnamed: D1.A, PEDALS.3, R5.P$2
unnamed: SOFTWARE_SHUTOFF.2, U$5.3
unnamed: LED1.C, R2.2
unnamed: LED2.C, R3.2
unnamed: LED3.C, R4.2
unnamed: R6.2, U$5.2
READ_CHARGE: BSPD.6, BSPD1:U$12.1, BSPD1:U$12.2, LED2.A, U$1.A8
READ_FAULT: BSPD.5, BSPD1:U$12.6, BSPD1:U$12.7, LED3.A, U$1.A7
READ_SWITCH: BSPD.7, BSPD1:U$10.6, BSPD1:U$10.7, LED1.A, U$1.A9
SHUTDOWN_A: BSPD.1, SOFTWARE_SHUTOFF.P
SHUTDOWN_B: BSPD1:U$1.P, SOFTWARE_SHUTOFF.S
SHUTDOWN_D: BSPD.2, BSPD1:U$3.7
SHUTDOWN_RELAY_CTRL: U$1.D12, U$5.1
SIGNAL_BRAKE: BSPD.4, BSPD1:CALIBRATE2.1, R5.P$1
SIGNAL_CURRENT: BSPD.3, BSPD1:CALIBRATE1.1
